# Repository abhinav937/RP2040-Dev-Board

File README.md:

# RP2040-Dev-Board
PCB Design(4 Layer) of Breadboard friendly RP2040 Dev Board with USB-C. <br /> 

#### Layer:

Layer 1: Front Cu <br /> 
Layer 2: Gnd <br /> 
Layer 3: Gnd <br /> 
Layer 4: Back Cu <br /> 

Initially my designs had inner layers as gnd and 3.3V, I got some netlist parity when I uploaded to my PCB manufacturer. But KiCad wasn't showing any errors in DRC, So I made both layers as Gnd.
#### Manufacturing
All components were purchased in [lcsc.com](lcsc.com) except RP2040, Which I purchased locally for 80Rs(~$1)/μC from robu.in. <br /> 

LCSC BOM: https://github.com/abhinav937/RP2040-Dev-Board/blob/main/RP2040_LCSC_BOM.csv <br /> 

I got my PCBs manufactured from [Aisler](aisler.net). <br /> 

Rev2 has lot of inspiration from michael rangen's PCB layout. Also I've used KiBuzzard for silkscreen texts, Which I personally like very much.
#### Refer my [documentation](https://github.com/abhinav937/RP2040-Dev-Board/blob/main/RP2040%20Dev%20Board%20Documentation_v01.pdf) for full information.

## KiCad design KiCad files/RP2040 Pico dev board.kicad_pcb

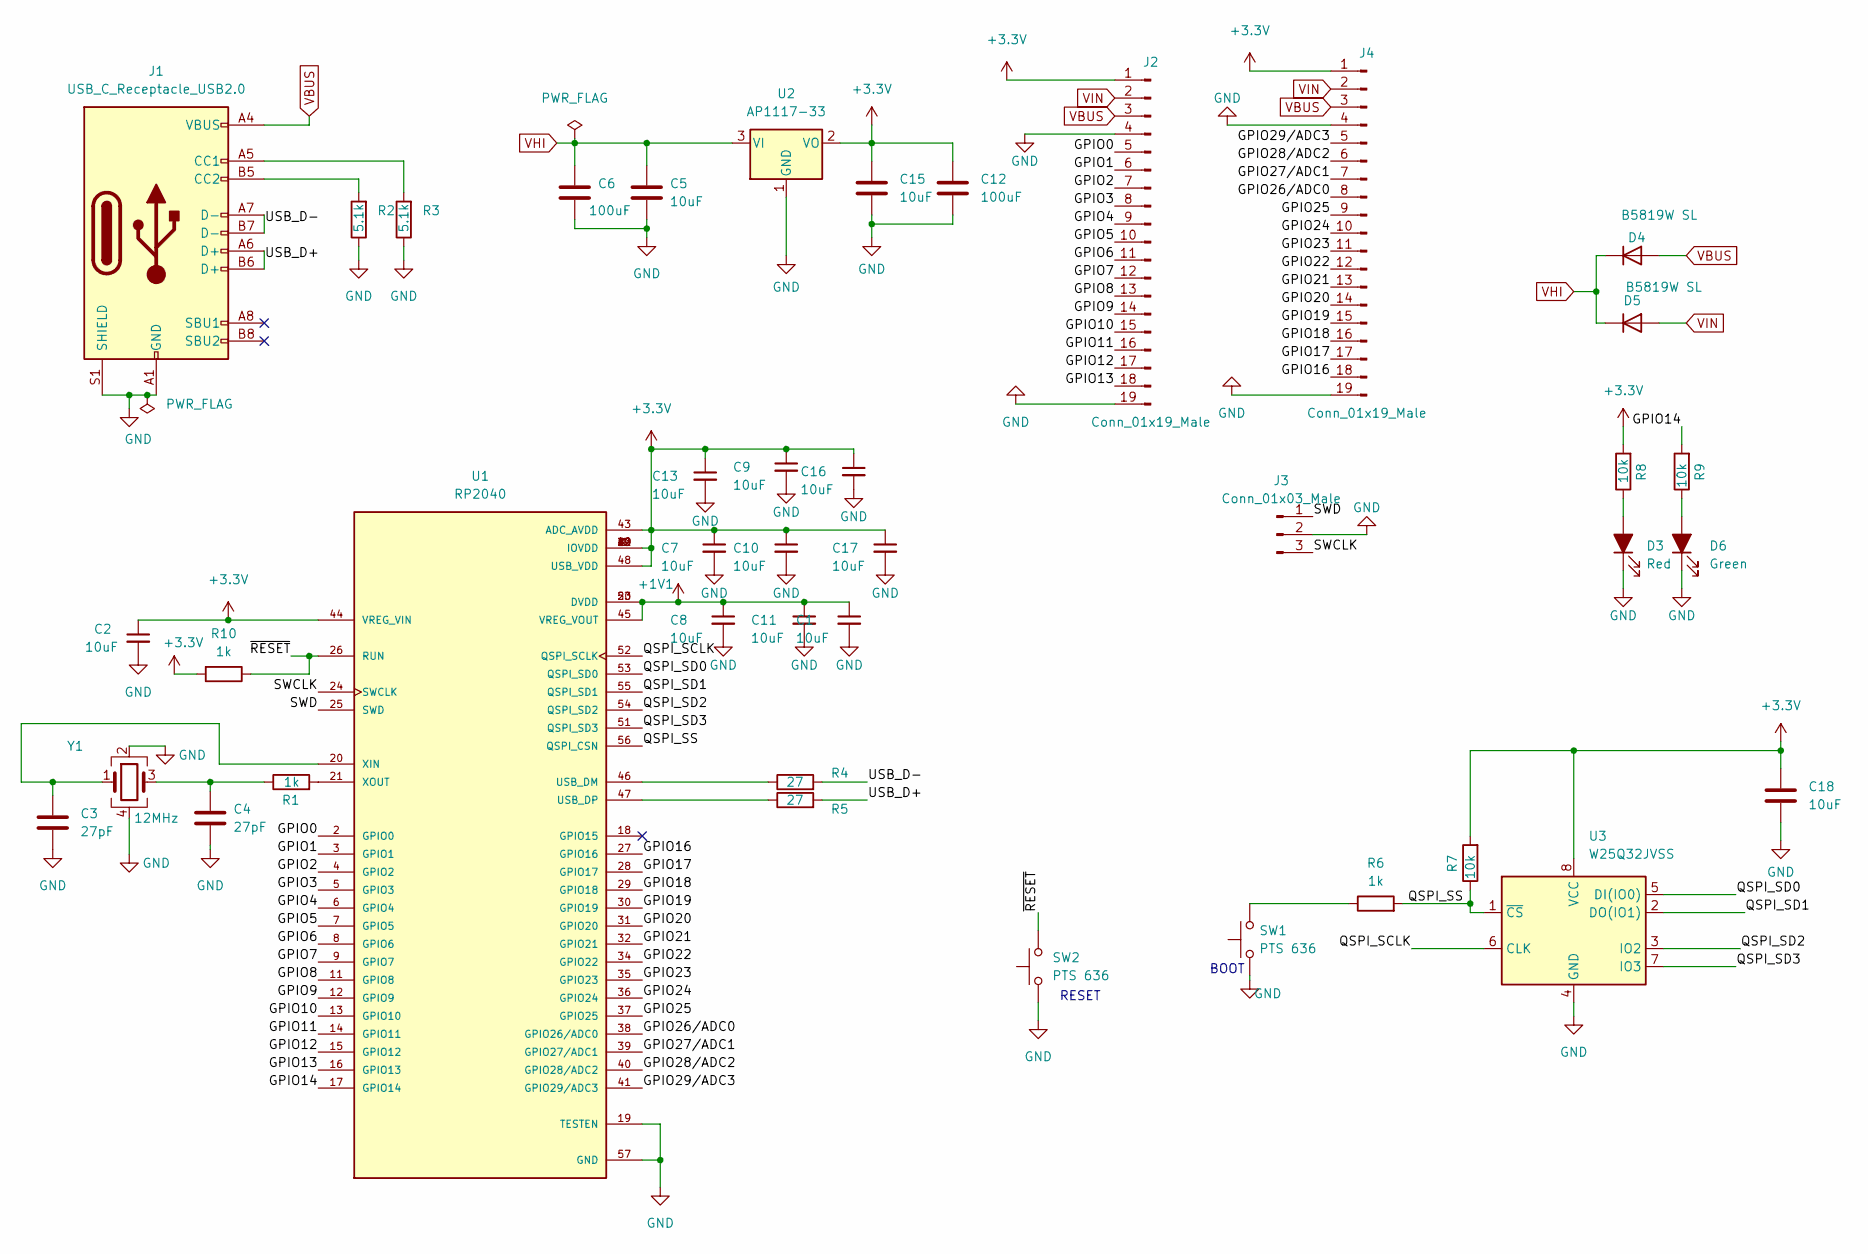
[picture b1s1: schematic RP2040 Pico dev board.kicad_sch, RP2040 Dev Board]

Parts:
C1, C2, C7, C8, C9, C10, C11, C13, C16, C17: 10uF; C_0402_1005Metric; JLCPCB P/N C15525
C3, C4: 27pF; C_0402_1005Metric
C5, C15, C18: 10uF; C_0402_1005Metric
C6, C12: 100uF; C_1206_3216Metric
D3: Red; LED_0805_2012Metric; JLCPCB P/N C2297
D4, D5: B5819W SL; D_SOD-123
D6: Green; LED_0805_2012Metric; JLCPCB P/N C2297
J1: USB_C_Receptacle_USB2.0; USB_C_Receptacle_Palconn_UTC16-G
J2, J4: Conn_01x19_Male; PinHeader_1x19_P2.54mm_Vertical
J3: Conn_01x03_Male; PinHeader_1x03_P2.54mm_Vertical
R1: 1k; R_0402_1005Metric; JLCPCB P/N C11702
R2, R3: 5.1k; R_0402_1005Metric
R4, R5: 27; R_0402_1005Metric; JLCPCB P/N C25100
R6, R10: 1k; R_0402_1005Metric
R7, R8, R9: 10k; R_0402_1005Metric; JLCPCB P/N C25744
SW1, SW2: PTS 636; PTS636SK25FSMTRLFS
U1: RP2040; QFN40P700X700X90-57N; PARTREV 1.6.1
U2: AP1117-33; SOT-89-3
U3: W25Q32JVSS; SOIC-8_5.23x5.23mm_P1.27mm
Y1: 12MHz; Crystal_SMD_3225-4Pin_3.2x2.5mm; JLCPCB P/N C9002

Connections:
+1V1: C1.1, C8.1, C11.1, U1.23 (DVDD), U1.45 (VREG_VOUT), U1.50 (DVDD)
+3V3: C2.1, C7.1, C9.1, C10.1, C12.1, C13.1, C15.1, C16.1, C17.1, C18.1, J2.1, J4.1, R7.2, R8.2, R10.2, U1.1 (IOVDD), U1.10 (IOVDD), U1.22 (IOVDD), U1.33 (IOVDD), U1.42 (IOVDD), U1.43 (ADC_AVDD), U1.44 (VREG_VIN), U1.48 (USB_VDD), U1.49 (IOVDD), U2.2 (VO), U3.8 (VCC)
/GPIO0: J2.5, U1.2 (GPIO0)
/GPIO1: J2.6, U1.3 (GPIO1)
/GPIO2: J2.7, U1.4 (GPIO2)
/GPIO3: J2.8, U1.5 (GPIO3)
/GPIO4: J2.9, U1.6 (GPIO4)
/GPIO5: J2.10, U1.7 (GPIO5)
/GPIO6: J2.11, U1.8 (GPIO6)
/GPIO7: J2.12, U1.9 (GPIO7)
/GPIO8: J2.13, U1.11 (GPIO8)
/GPIO9: J2.14, U1.12 (GPIO9)
/GPIO10: J2.15, U1.13 (GPIO10)
/GPIO11: J2.16, U1.14 (GPIO11)
/GPIO12: J2.17, U1.15 (GPIO12)
/GPIO13: J2.18, U1.16 (GPIO13)
/GPIO14: R9.2, U1.17 (GPIO14)
/GPIO16: J4.18, U1.27 (GPIO16)
/GPIO17: J4.17, U1.28 (GPIO17)
/GPIO18: J4.16, U1.29 (GPIO18)
/GPIO19: J4.15, U1.30 (GPIO19)
/GPIO20: J4.14, U1.31 (GPIO20)
/GPIO21: J4.13, U1.32 (GPIO21)
/GPIO22: J4.12, U1.34 (GPIO22)
/GPIO23: J4.11, U1.35 (GPIO23)
/GPIO24: J4.10, U1.36 (GPIO24)
/GPIO25: J4.9, U1.37 (GPIO25)
/GPIO26/ADC0: J4.8, U1.38 (GPIO26/ADC0)
/GPIO27/ADC1: J4.7, U1.39 (GPIO27/ADC1)
/GPIO28/ADC2: J4.6, U1.40 (GPIO28/ADC2)
/GPIO29/ADC3: J4.5, U1.41 (GPIO29/ADC3)
/QSPI_SCLK: U1.52 (QSPI_SCLK), U3.6 (CLK)
/QSPI_SD0: U1.53 (QSPI_SD0), U3.5 (DI(IO0))
/QSPI_SD1: U1.55 (QSPI_SD1), U3.2 (DO(IO1))
/QSPI_SD2: U1.54 (QSPI_SD2), U3.3 (IO2)
/QSPI_SD3: U1.51 (QSPI_SD3), U3.7 (IO3)
/QSPI_SS: R6.2, R7.1, U1.56 (QSPI_CSN), U3.1 (~CS)
/SWCLK: J3.3, U1.24 (SWCLK)
/SWD: J3.1, U1.25 (SWD)
/USB_D+: J1.A6 (D+), J1.B6 (D+), R5.2
/USB_D-: J1.A7 (D-), J1.B7 (D-), R4.2
/~RESET: R10.1, SW2.2, U1.26 (RUN)
GND: C1.2, C2.2, C3.2, C4.2, C5.2, C6.2, C7.2, C8.2, C9.2, C10.2, C11.2, C12.2, C13.2, C15.2, C16.2, C17.2, C18.2, D3.1 (K), D6.1 (K), J1.A1 (GND), J1.A12 (GND), J1.B1 (GND), J1.B12 (GND), J1.S1 (SHIELD), J2.4, J2.19, J3.2, J4.4, J4.19, R2.1, R3.1, SW1.1, SW2.1, U1.19 (TESTEN), U1.57 (GND), U2.1 (GND), U3.4 (GND), Y1.2, Y1.4
unnamed: C3.1, U1.20 (XIN), Y1.1
unnamed: C4.1, R1.1, Y1.3
unnamed: D3.2 (A), R8.1
unnamed: D6.2 (A), R9.1
unnamed: J1.A5 (CC1), R3.2
unnamed: J1.B5 (CC2), R2.2
unnamed: R1.2, U1.21 (XOUT)
unnamed: R4.1, U1.46 (USB_DM)
unnamed: R5.1, U1.47 (USB_DP)
unnamed: R6.1, SW1.2
VBUS: D4.2 (A), J1.A4 (VBUS), J1.A9 (VBUS), J1.B4 (VBUS), J1.B9 (VBUS), J2.3, J4.3
VHI: C5.1, C6.1, D4.1 (K), D5.1 (K), U2.3 (VI)
VIN: D5.2 (A), J2.2, J4.2

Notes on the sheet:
BOOT
RESET

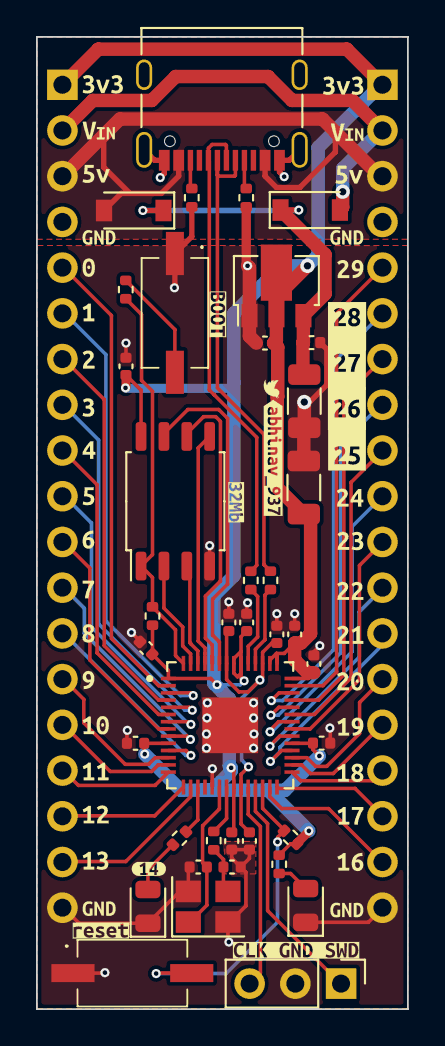
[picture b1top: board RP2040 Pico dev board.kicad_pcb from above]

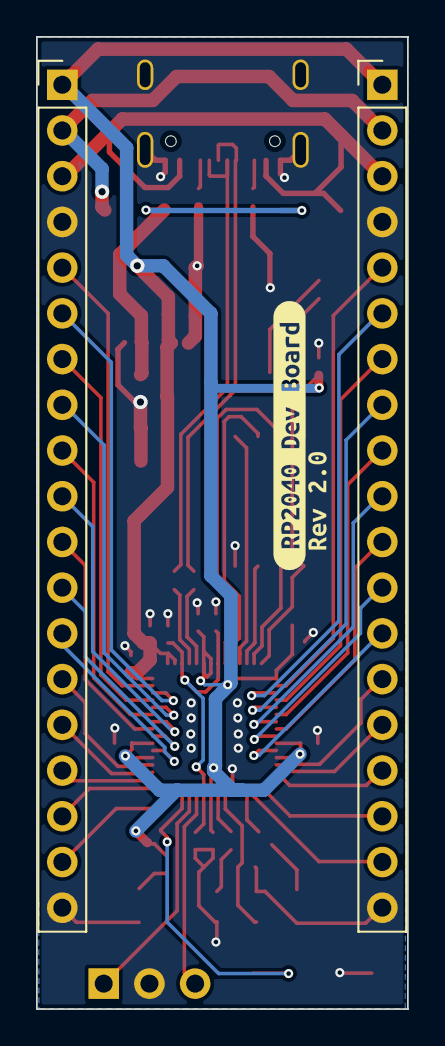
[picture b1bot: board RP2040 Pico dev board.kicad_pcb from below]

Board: 4 copper layers, 20.6 x 54.0 mm, 90 parts (4 on the bottom side), 56 nets.

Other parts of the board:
G: LOGO; Twitter-logo
kibuzzard-630E1CDD: G***; kibuzzard-630E1CDD
kibuzzard-630E1CF2: G***; kibuzzard-630E1CF2
kibuzzard-630E1CFE: G***; kibuzzard-630E1CFE
kibuzzard-630E1D4B: G***; kibuzzard-630E1D4B
kibuzzard-630E1D5E: G***; kibuzzard-630E1D5E
kibuzzard-630E1D7D: G***; kibuzzard-630E1D7D
kibuzzard-630E1D11: G***; kibuzzard-630E1D11
kibuzzard-630E1D29: G***; kibuzzard-630E1D29
kibuzzard-630E1D34: G***; kibuzzard-630E1D34
kibuzzard-630E1D55: G***; kibuzzard-630E1D55
kibuzzard-630E1D68: G***; kibuzzard-630E1D68
kibuzzard-630E1D83: G***; kibuzzard-630E1D83
kibuzzard-630E1D93: G***; kibuzzard-630E1D93
kibuzzard-630E1DDD: G***; kibuzzard-630E1DDD
kibuzzard-630E1E9D, kibuzzard-630E1E9D#2: G***; kibuzzard-630E1E9D
kibuzzard-630E1E94, kibuzzard-630E1E94#2: G***; kibuzzard-630E1E94
kibuzzard-630E1EE1, kibuzzard-630E1EE1#2: G***; kibuzzard-630E1EE1
kibuzzard-630E1EF5, kibuzzard-630E1EF5#2: G***; kibuzzard-630E1EF5
kibuzzard-630E1F07, kibuzzard-630E1F07#2, kibuzzard-630E1F07#3, kibuzzard-630E1F07#4: G***; kibuzzard-630E1F07
kibuzzard-630E1F17: G***; kibuzzard-630E1F17
kibuzzard-630E20A5: G***; kibuzzard-630E20A5
kibuzzard-630E20AD: G***; kibuzzard-630E20AD
kibuzzard-630E20BA: G***; kibuzzard-630E20BA
kibuzzard-630E20C1: G***; kibuzzard-630E20C1
kibuzzard-630E20C7: G***; kibuzzard-630E20C7
kibuzzard-630E20CF: G***; kibuzzard-630E20CF
kibuzzard-630E20DA: G***; kibuzzard-630E20DA
kibuzzard-630E20E0: G***; kibuzzard-630E20E0
kibuzzard-630E21C9: G***; kibuzzard-630E21C9
kibuzzard-630E22AA: G***; kibuzzard-630E22AA
kibuzzard-630E24DB: G***; kibuzzard-630E24DB
kibuzzard-630E27BD: G***; kibuzzard-630E27BD
kibuzzard-630E27EE: G***; kibuzzard-630E27EE
kibuzzard-630E209E: G***; kibuzzard-630E209E
kibuzzard-630E217B: G***; kibuzzard-630E217B
kibuzzard-630E260B: G***; kibuzzard-630E260B
kibuzzard-630E262A: G***; kibuzzard-630E262A
kibuzzard-630E263B: G***; kibuzzard-630E263B
kibuzzard-630E264D: G***; kibuzzard-630E264D
kibuzzard-630E2104: G***; kibuzzard-630E2104
kibuzzard-630E2223: G***; kibuzzard-630E2223

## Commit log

2022-09-14 Initial Upload of Rev2
2022-09-15 added LCSC BOM
2022-10-12 added documentation
2022-10-12 Added photos
2022-12-19 Spelling Error
